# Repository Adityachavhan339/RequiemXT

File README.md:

# RequiemXT 🎮
RequiemXT is Custom Wired USB Controller.

The Parts I Am Using:

- Waveshare RP2040-Zero Raspberry Pi MCU With Pre Soldered Header
- USB-C wired connection
- Electronic Spices 6 X 6 X 5mm Blue Color Touch Transient Horn Type Push Button Switch Pack of 20pcs
- Jumper Wire Female From Female (40 pcs)
- Robocraze PS2 Joystick Module Dual Axis Analog Sensor Push Button Switch
- Custom 2-Layer Controller Carrier Board
- #All Parts Link With Prices Is Available In BOM.csv and md.# 

Schematic Image:

PCB Image:

#Why I Made It
So It started Because I Hate Analog Triggers , Vibration Motors or Any Unnecessary Bluetooth Battery Type Things ( And I Couldn't Find Good Idea For A Project For Half Life 😓)

## HOW THIS WAS MADE
The schematic and PCB were made in KiCad.
1. First, I added the RP2040 to KiCad since it isn't included in the default libraries (the RP2040 ZIP file is available in the PCB design files directory).
2. I added all the buttons. Because there are no triggers or bumpers, the button count increased to 14 instead of the standard 12.
3. The PCB was routed using the Freerouting plugin in KiCad.

##FIRMWARE

I Never Have Wrote Firmware nor anything in C so still working on it. Though I Will Upload A Compatible Opensource Firmware for anyone who doesn't want to use what i will write 😅( Don't Use it i don't even know what i am going to do)

## AI DISCLOSURE
AI Didn't Made It, I Made It.
AI Was Only Used For Understanding How KiCad Works

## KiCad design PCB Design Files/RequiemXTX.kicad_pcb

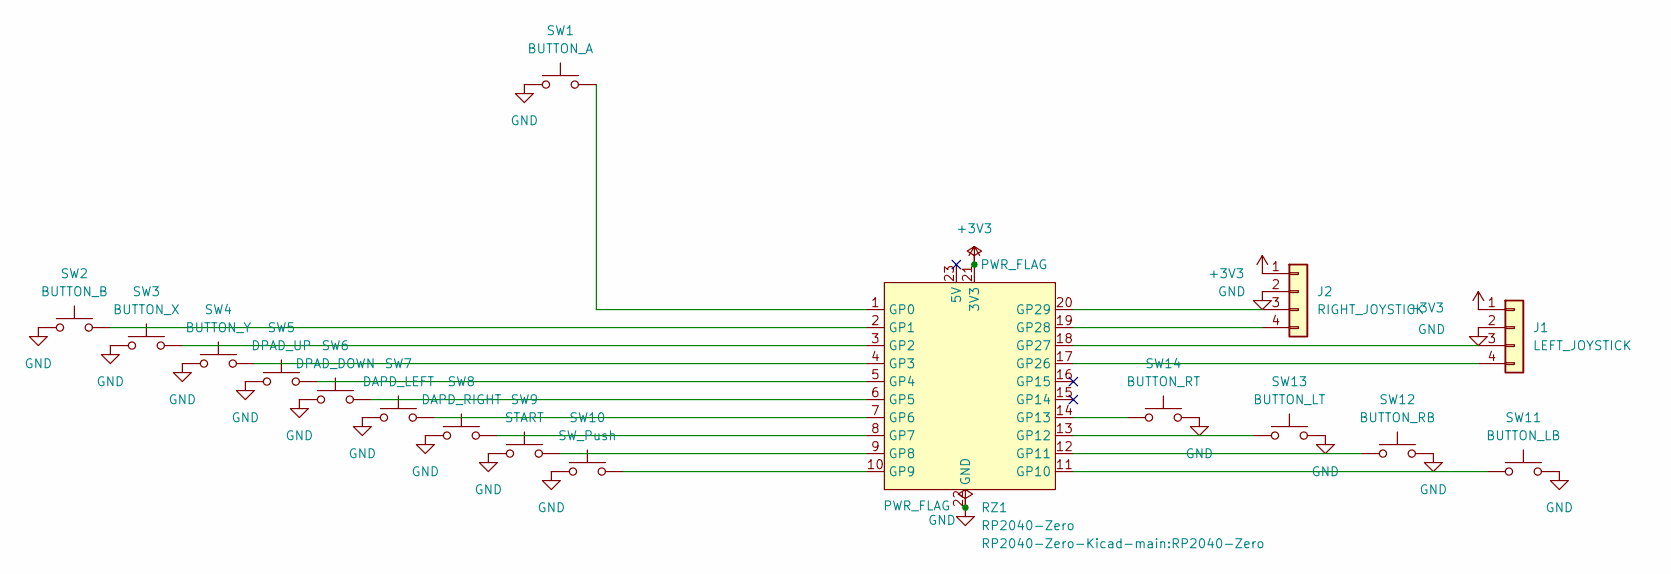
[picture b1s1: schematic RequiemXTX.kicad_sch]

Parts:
J1: LEFT_JOYSTICK; PinHeader_1x04_P2.54mm_Vertical
J2: RIGHT_JOYSTICK; PinHeader_1x04_P2.54mm_Vertical
RZ1: RP2040-Zero
SW1: BUTTON_A; SW_NKK_GW12LJP
SW2: BUTTON_B; SW_PUSH_6mm
SW3: BUTTON_X; SW_PUSH_6mm
SW4: BUTTON_Y; SW_PUSH_6mm
SW5: DPAD_UP; SW_PUSH_6mm
SW6: DPAD_DOWN; SW_PUSH_6mm
SW7: DAPD_LEFT; SW_PUSH_6mm
SW8: DAPD_RIGHT; SW_PUSH_6mm
SW9: START; SW_PUSH_6mm
SW10: SW_Push; SW_PUSH_6mm
SW11: BUTTON_LB; SW_PUSH_6mm
SW12: BUTTON_RB; SW_PUSH_6mm
SW13: BUTTON_LT; SW_PUSH_6mm
SW14: BUTTON_RT; SW_PUSH_6mm

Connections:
+3V3: J1.1, J2.1, RZ1.21 (3V3)
GND: J1.2, J2.2, RZ1.22 (GND), SW1.1, SW2.1, SW3.1, SW4.1, SW5.1, SW6.1, SW7.1, SW8.1, SW9.1, SW10.1, SW11.2, SW12.2, SW13.2, SW14.2
unnamed: J1.3, RZ1.18 (GP27)
unnamed: J1.4, RZ1.17 (GP26)
unnamed: J2.3, RZ1.20 (GP29)
unnamed: J2.4, RZ1.19 (GP28)
unnamed: RZ1.1 (GP0), SW1.2
unnamed: RZ1.2 (GP1), SW2.2
unnamed: RZ1.3 (GP2), SW3.2
unnamed: RZ1.4 (GP3), SW4.2
unnamed: RZ1.5 (GP4), SW5.2
unnamed: RZ1.6 (GP5), SW6.2
unnamed: RZ1.7 (GP6), SW7.2
unnamed: RZ1.8 (GP7), SW8.2
unnamed: RZ1.9 (GP8), SW9.2
unnamed: RZ1.10 (GP9), SW10.2
unnamed: RZ1.11 (GP10), SW11.1
unnamed: RZ1.12 (GP11), SW12.1
unnamed: RZ1.13 (GP12), SW13.1
unnamed: RZ1.14 (GP13), SW14.1

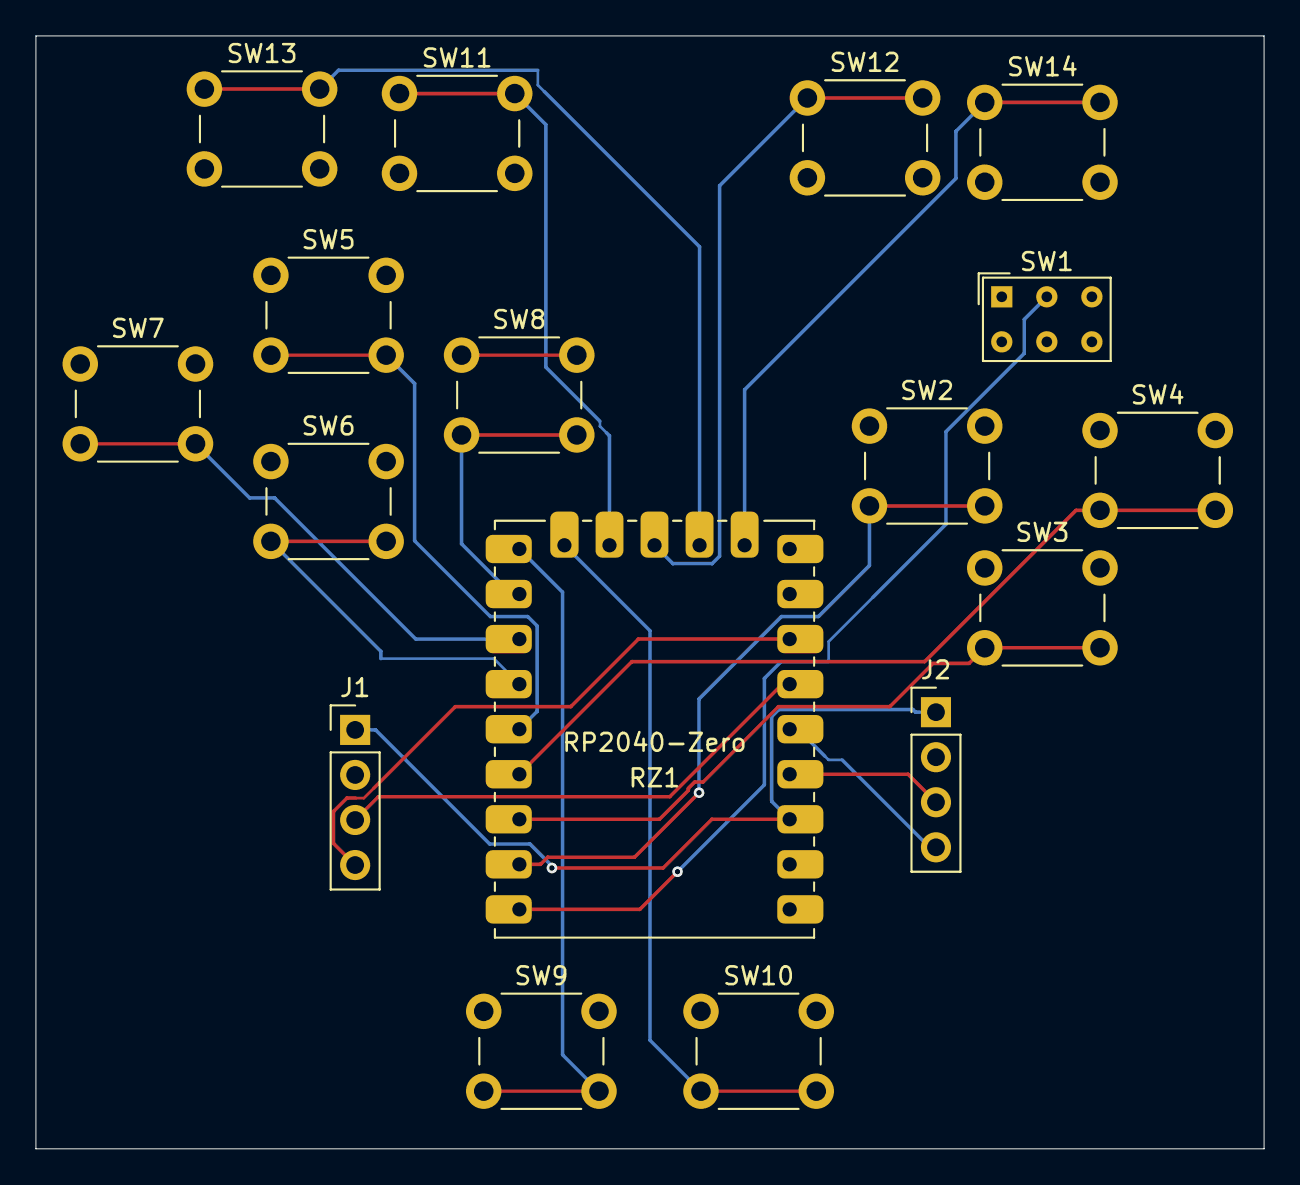
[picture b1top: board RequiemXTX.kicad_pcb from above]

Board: 2 copper layers, 69.2 x 62.8 mm, 17 parts (0 on the bottom side), 20 nets.
